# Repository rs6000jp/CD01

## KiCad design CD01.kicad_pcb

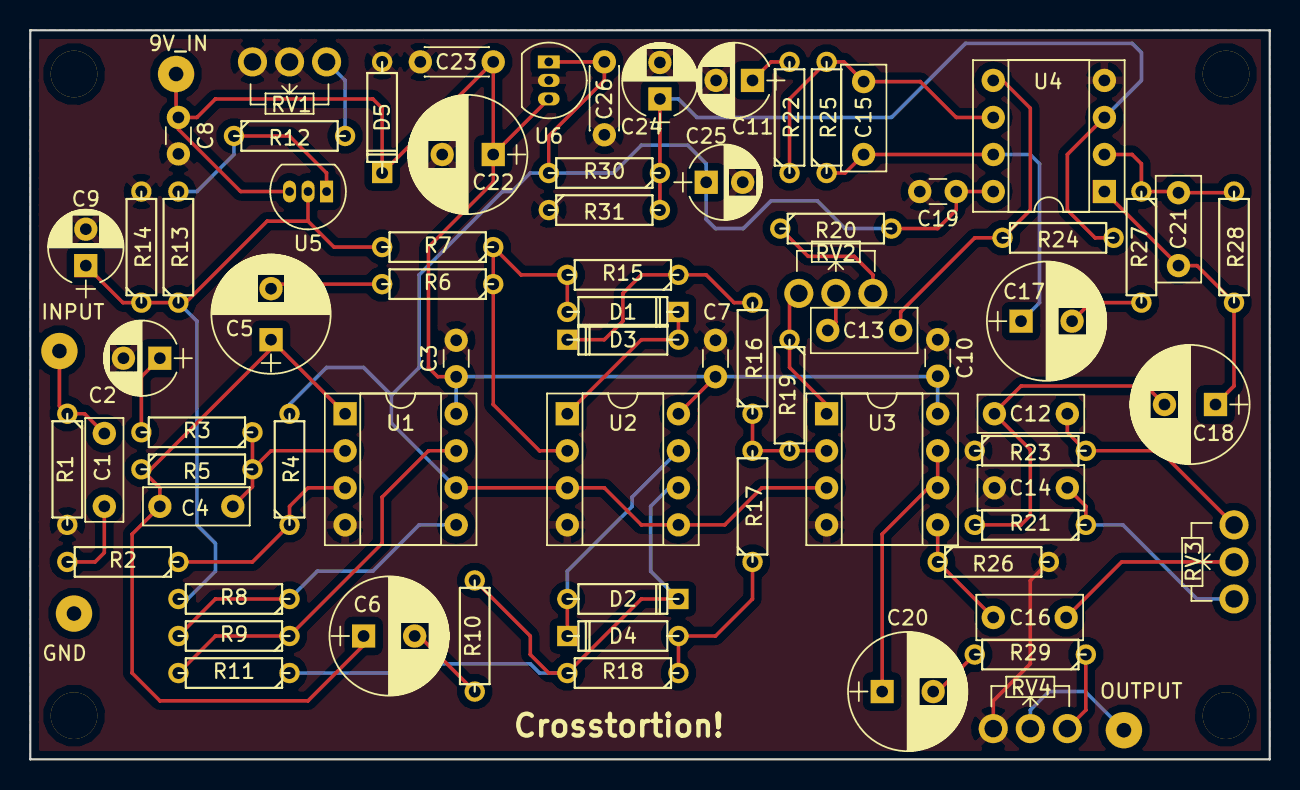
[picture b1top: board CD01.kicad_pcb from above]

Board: 2 copper layers, 85.0 x 50.0 mm, 76 parts (0 on the bottom side), 43 nets.

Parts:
9V_IN: 9V_IN; SolderWirePad_single_1mmDrill
C1: 100n; C_Rect_L7.0mm_W2.5mm_P5.00mm
C2, C9, C11, C25, C26: 10u; CP_Radial_D5.0mm_P2.50mm
C3, C7, C8, C10, C19: 100n; C_Disc_D3.0mm_W1.6mm_P2.50mm
C4: 1n; C_Rect_L7.2mm_W2.5mm_P5.00mm_FKS2_FKP2_MKS2_MKP2
C5, C6, C17, C18, C20: 10uF BP; CP_Radial_D8.0mm_P3.50mm
C12: 3.3n; C_Rect_L7.2mm_W2.5mm_P5.00mm_FKS2_FKP2_MKS2_MKP2
C13, C16: 100n; C_Rect_L7.2mm_W3.0mm_P5.00mm_FKS2_FKP2_MKS2_MKP2
C14: 10n; C_Rect_L7.2mm_W3.0mm_P5.00mm_FKS2_FKP2_MKS2_MKP2
C15, C21: 470p; C_Rect_L7.2mm_W3.0mm_P5.00mm_FKS2_FKP2_MKS2_MKP2
C22: 100u; CP_Radial_D8.0mm_P3.50mm
C23, C24: 100n; C_Disc_D4.3mm_W1.9mm_P5.00mm
D1, D2, D3, D4: 1N4148; D3
D5: 1N4007; D3
GND: GND; SolderWirePad_single_1mmDrill
INPUT: INPUT; SolderWirePad_single_1mmDrill
OUTPUT: OUTPUT; SolderWirePad_single_1mmDrill
R1: 2.2M; R3
R2, R13, R14, R29: 1K; R3
R3, R6, R7, R8, R9, R10, R11, R15, R16, R17, R18, R19, R22, R27, R30, R31: 10K; R3
R4: 1M; R3
R5, R24, R26: 100K; R3
R12: 2.7K; R3
R20: 470R; R3
R21, R23: 22K; R3
R25, R28: 220K; R3
RV1: 1KA; Potentiometer_WirePads_Small
RV2, RV3: 100KB; Potentiometer_WirePads_Small
RV4: 100KA; Potentiometer_WirePads_Small
U1: TL072; DIP-8_W7.62mm_Socket
U2, U3, U4: 4558; DIP-8_W7.62mm_Socket
U5: LM317AT; TO-92_Inline_Narrow_Oval
U6: NJM78L00; TO-92_Inline_Narrow_Oval

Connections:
5-6V: C9.1, R7.2, R8.2, R13.1, R14.1, U5.2
+2.5V: C26.1, R24.2, R30.1, R31.2, U4.3
+5V: C19.1, C24.1, C25.1, R4.2, R20.2, R30.2, U1.6, U2.3, U2.5, U3.3, U4.8, U6.1
+9V: 9V_IN.1, C3.1, C7.1, C8.1, C10.2, C22.1, C23.1, D5.1, U1.8, U2.8, U3.8, U5.3, U6.3
GND: C2.2, C3.2, C7.2, C8.2, C9.2, C10.1, C11.2, C14.2, C19.2, C22.2, C23.2, C24.2, C25.2, C26.2, D5.2, R1.2, R14.2, R23.1, R26.2, R31.1, RV1.2, RV1.3, RV4.1, U1.4, U2.4, U3.4, U4.4, U6.2
unnamed: C1.1, R2.2
unnamed: C1.2, INPUT.1, R1.1
unnamed: C2.1, R3.2
unnamed: C4.1, C5.1, C6.1, R5.1, U1.1
unnamed: C4.2, R3.1, R5.2, U1.2
unnamed: C5.2, R6.2
unnamed: C6.2, R10.2
unnamed: C11.1, R22.2
unnamed: C12.1, R23.2, RV3.3
unnamed: C12.2, C18.2, R21.2
unnamed: C13.1, R24.1, U4.5
unnamed: C13.2, RV2.2
unnamed: C14.1, R21.1, RV3.1
unnamed: C15.1, C17.1, R25.1, U4.7
unnamed: C15.2, R22.1, R25.2, U4.6
unnamed: C16.1, R26.1, U3.5
unnamed: C16.2, RV3.2
unnamed: C17.2, R27.2
unnamed: C18.1, C21.1, R28.1, U4.1
unnamed: C20.1, U3.6, U3.7
unnamed: C20.2, R29.2
unnamed: C21.2, R27.1, R28.2, U4.2
unnamed: D1.1, D3.2, U2.1
unnamed: D1.2, R6.1, R7.1, R15.2, U2.2
unnamed: D2.1, R10.1, R11.1, R18.2, U2.6
unnamed: D2.2, D4.1, U2.7
unnamed: D3.1, R15.1, R16.2
unnamed: D4.2, R17.1, R18.1
unnamed: OUTPUT.1, RV4.2
unnamed: R2.1, R4.1, U1.3
unnamed: R8.1, R9.2, U1.5
unnamed: R9.1, R11.2, U1.7
unnamed: R12.1, R13.2, U5.1
unnamed: R12.2, RV1.1
unnamed: R16.1, R17.2, R19.2, U3.2
unnamed: R19.1, RV2.1, U3.1
unnamed: R20.1, RV2.3
unnamed: R29.1, RV4.3

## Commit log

2018-03-31 Crosstorion
    first
2018-03-31 Revert "Crosstorion"
    This reverts commit 17a37ec551334da2fd042a3322f43aa35ee325cb.
